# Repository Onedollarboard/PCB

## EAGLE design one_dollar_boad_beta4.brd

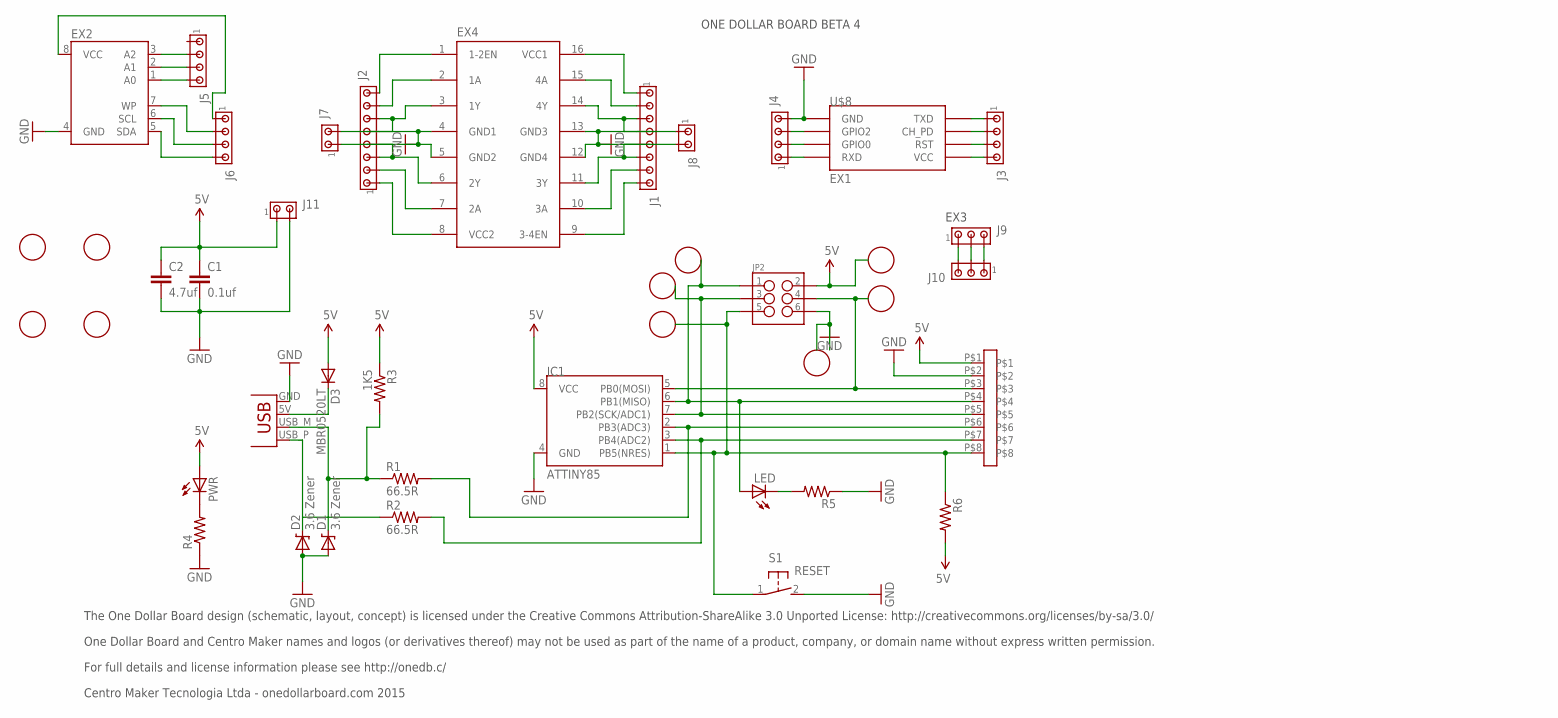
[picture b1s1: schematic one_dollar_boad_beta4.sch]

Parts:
C1: 0.1uf; 0402-CAP
C2: 4.7uf; 0805
CONNECTORBAR1: .; FEMEABARRA01X08
D1, D2: 3.6 Zener; SOD-323
D3: MBR0520LT; SOD123
EX2: AT24CP; DIL08
EX4: L293D; DIL16
IC1: ATTINY85; SO08-EIAJ
ICSP1, ICSP2, ICSP3, ICSP4, ICSP5, ICSP6: ICSP
J1, J2: MTA08-100; 10X08MTA
J3, J4, J5, J6: MTA04-100; 10X04MTA
J7, J8, J11: MTA02-100; 10X02MTA
J9, J10: MTA03-100; 10X03MTA
JP2: M03X22X3_SILK_MALE_PTH; 2X3
LED: LED0603; LED-0603
PWR: LED0603; LED-0603
R1, R2: 66.5R; 0402-RES
R3: 1K5; 0402-RES
R4, R5, R6: RESISTOR0402-RES; 0402-RES
S1: RESET; DTSM-3
U$8: EX1; ESP01
U$9: ARDUINOPINAGEM
X1: USBPCB; USB-A-PCB

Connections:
5V: C1.1, C2.1, CONNECTORBAR1.P$1, D3.A, IC1.8 (VCC), J11.1, JP2.2, PWR.A, R3.1, R6.2
EX1: EX4.15 (4A), J1.2
GND: C1.2, C2.2, CONNECTORBAR1.P$2, D1.2 (A), D2.2 (A), EX2.4 (GND), EX4.4 (GND1), EX4.5 (GND2), EX4.12 (GND4), EX4.13 (GND3), IC1.4 (GND), J1.4, J1.5, J2.4, J2.5, J4.4, J11.2, JP2.6, R4.1, R5.1, S1.2, U$8.GND, X1.GND
unnamed: J9.1, J10.3
unnamed: CONNECTORBAR1.P$3, IC1.5 (PB0(MOSI)), JP2.4
unnamed: CONNECTORBAR1.P$4, IC1.6 (PB1(MISO)), JP2.1, LED.A
unnamed: CONNECTORBAR1.P$5, IC1.7 (PB2(SCK/ADC1)), JP2.3
unnamed: CONNECTORBAR1.P$7, IC1.3 (PB4(ADC2)), R2.2
unnamed: EX4.1 (1-2EN), J2.8
unnamed: EX4.2 (1A), J2.7
unnamed: D1.1 (C), R1.1, R3.2, X1.USB_M (D-)
unnamed: D2.1 (C), R2.1, X1.USB_P (D+)
unnamed: LED.C, R5.2
unnamed: EX2.8 (VCC), J6.1
unnamed: EX2.7 (WP), J6.2
unnamed: EX4.3 (1Y), J2.6, J7.2
unnamed: D3.C, X1.5V (VBUS)
unnamed: PWR.C, R4.2
unnamed: EX4.8 (VCC2), J2.1
unnamed: EX4.7 (2A), J2.2
unnamed: EX4.6 (2Y), J2.3, J7.1
unnamed: EX4.16 (VCC1), J1.1
unnamed: EX2.6 (SCL), J6.3
unnamed: EX2.5 (SDA), J6.4
unnamed: EX4.14 (4Y), J1.3, J8.1
unnamed: EX4.9 (3-4EN), J1.8
unnamed: EX4.10 (3A), J1.7
unnamed: EX2.3 (A2), J5.2
unnamed: J4.3, U$8.GPIO2
unnamed: J4.2, U$8.GPIO0
unnamed: J4.1, U$8.RX (RXD)
unnamed: J3.1, U$8.TX (TXD)
unnamed: J3.2, U$8.CH_PD
unnamed: J3.3, U$8.RST
unnamed: J3.4, U$8.VCC
unnamed: EX2.2 (A1), J5.3
unnamed: EX2.1 (A0), J5.4
unnamed: EX4.11 (3Y), J1.6, J8.2
unnamed: J9.2, J10.2
unnamed: CONNECTORBAR1.P$6, IC1.2 (PB3(ADC3)), R1.2
unnamed: CONNECTORBAR1.P$8, IC1.1 (PB5(NRES)), JP2.5, R6.1, S1.1
unnamed: J9.3, J10.1

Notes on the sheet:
The One Dollar Board design (schematic, layout, concept) is licensed under the Creative Commons Attribution-ShareAlike 3.0 Unported License: http://creativecommons.org/licenses/by-sa/3.0/
One Dollar Board and Centro Maker names and logos (or derivatives thereof) may not be used as part of the name of a product, company, or domain name without express written permission.
For full details and license information please see http://onedb.c/
Centro Maker Tecnologia Ltda - onedollarboard.com 2015
ONE DOLLAR BOARD BETA 4
EX3

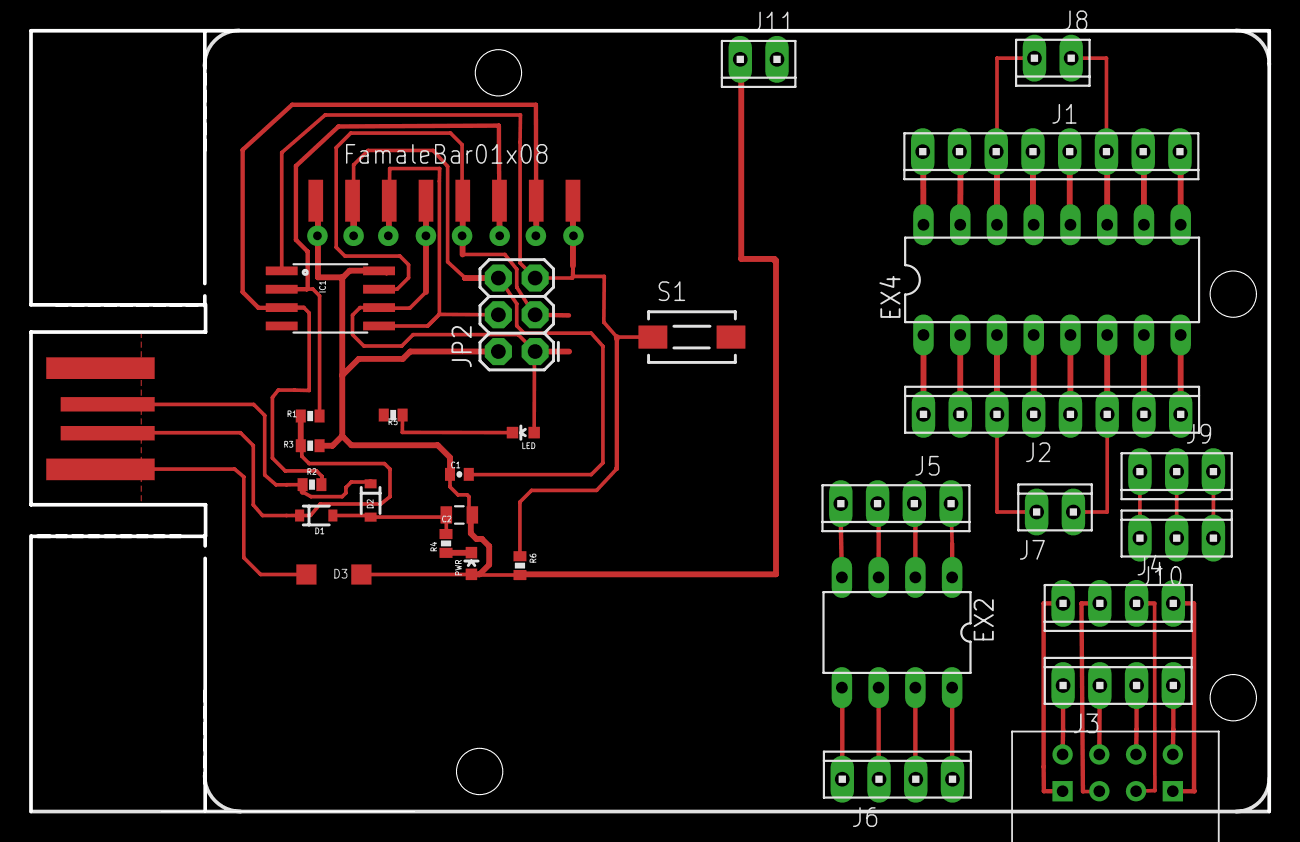
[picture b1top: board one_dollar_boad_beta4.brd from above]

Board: 2 copper layers, 85.6 x 54.0 mm, 39 parts (0 on the bottom side), 42 nets.

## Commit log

2016-04-05 - Nomeação dos pinos do CI L293 - Reposicionado o CI 24C256 para facilitar a leitura da nomeação dos pinos do CI L293 - Nomeado os pinos do EPS - Adicionado o resistor de 10K (Pull-up) no pino RESET
2016-04-06 `
    - Adicionado slot para LD1117
    - Adicionado Silk
    - Cantos chanfrados
    - Retirado GND dos componentes de expansão para que o usuário possa usar os expansores que achar melhor.
2016-04-07 Pinos ESP8266
    Adicionado numeração de identificação para os pinos do ESP8266
2016-04-07 Pinos ESP8266
2016-04-07 Added files via upload
2016-04-07 Rename one_dollar_boad_rev4.brd to one_dollar_boad_beta4.brd
2016-04-07 Rename one_dollar_boad_rev4.sch to one_dollar_boad_beta4.sch
2016-04-07 O Arquivo foi duplicado.
2016-04-07 Modificação feita por Marcelo Cuin
2016-04-09 Pinos reposicionados
2016-04-09 Eliminado nomes de CIs
    Motivo: pode confundir usuarios
2016-04-09 Nome adicionado One Dollar Board Beta 4
2016-04-09 Adicionado nome de pinos e mudança de lugar de RST
    Colocado números e descrição de PINOS
    Mudança de lugar de Botão RESET
2016-04-09 Adicionado borda inferior faltante
2016-04-09 Numero 5 conector ESP8266 faltante corrigido
2016-04-09 aumentada espessura das trilhas do ESP8266
2016-04-12 GND retirado
2016-04-21 Added files via upload
    Adicionado alimentação externa

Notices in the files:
one_dollar_boad_beta4.brd:
"One Dollar Board" name. logo and Centro Maker name, logo Copyright 2015 Centro Maker Tecnologia Ltda. and Claudio Olmedo All Rights Reserved
The "One Dollar Board" Desing (schematic, layout, concept) is licensed under the Creative Commons Attribution-ShareAlike 3.0 Unported License: http://creativecommons.org/licenses/by-sa/3.0
parts and their libraries:
SparkFun: Licensing: CC v3.0 Share-Alike You are welcome to use this library for commercial purposes.
